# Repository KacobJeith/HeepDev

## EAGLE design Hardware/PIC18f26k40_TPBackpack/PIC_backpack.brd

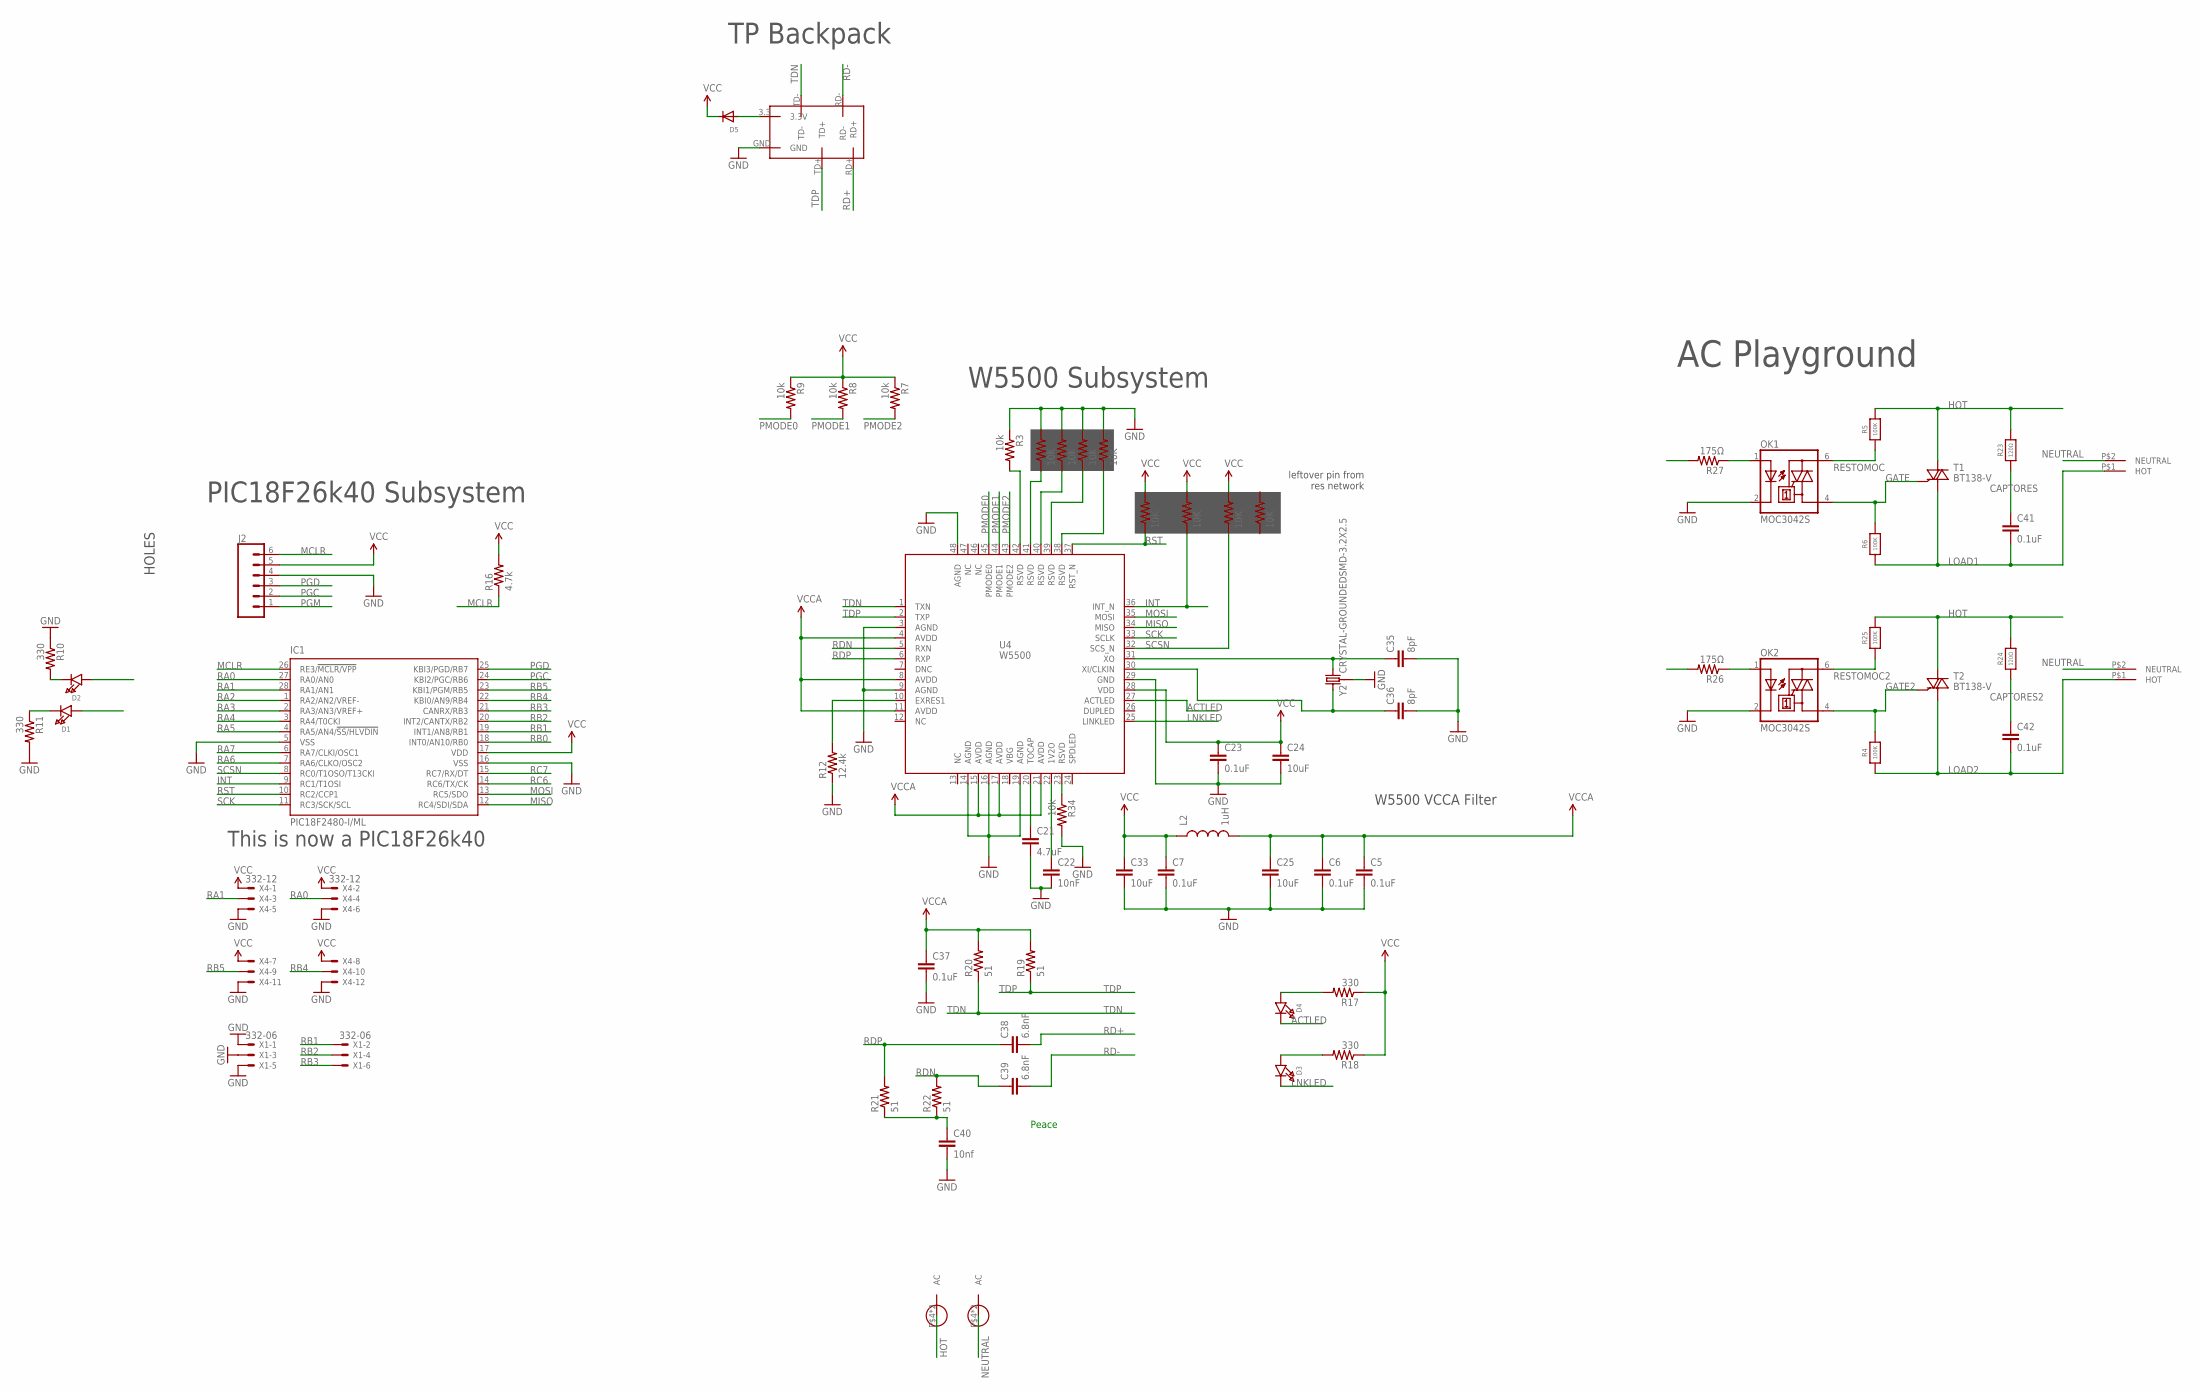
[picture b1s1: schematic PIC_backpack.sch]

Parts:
C5, C6, C7, C23, C37: 0.1uF; 0603-CAP
C21: 4.7uF; 0603-CAP
C22: 10nF; 0603-CAP
C24, C25, C33: 10uF; 0603-CAP
C35, C36: 8pF; 0603-CAP
C38, C39: 6.8nF; 0603-CAP
C40: 10nf; 0603-CAP
C41, C42: 0.1uF; 1210
D1, D2, D3, D4: LED0603_NOOUTLINE; CHIPLED_0603_NOOUTLINE
D5: DIODESOD-123; SOD-123
IC1: PIC18F2480-I/ML; QFN28-ML_6X6MM
J2: CONN_06NO_SILK_FEMALE_PTH; 1X06_NO_SILK
L2: 1uH; 0603
OK1, OK2: MOC3042S; DIL6-SMD
R1, R2: 10K; RESPACK_4X0603
R3, R7, R8, R9, R34: 10k; 0603-RES
R4, R5, R6, R25: 100K; 0805_10MGAP
R10, R11, R17, R18: 330; 0603-RES
R12: 12.4k; 0603-RES
R16: 4.7k; 0603-RES
R19, R20, R21, R22: 51; 0603-RES
R23, R24: 120Ω; 0805_10MGAP
R26, R27: 175Ω; 0603-RES
T1, T2: BT138-V; TO220BV
U4: W5500
U$1: TPLINK_BACKPACK; BACKPACK_WITH_PROTO
U$2, U$3: AC_BLADE
U$4, U$5: AC_TERMINAL
X1: 332-06
X4: 332-12
Y2: CRYSTAL-GROUNDEDSMD-3.2X2.5; CRYSTAL-SMD-3.2X2.5MM

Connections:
ACTLED: D4.C, U4.27 (ACTLED)
CAPTORES: C41.1, R23.1
CAPTORES2: C42.1, R24.1
GATE: OK1.4 (A1), R6.2, T1.G
GATE2: OK2.4 (A1), R4.2, T2.G
GND: C5.2, C6.2, C7.2, C21.2, C22.2, C23.2, C24.2, C25.2, C33.2, C35.2, C36.2, C37.2, C40.2, IC1.5 (VSS), IC1.16 (VSS), J2.4, OK1.2 (C), OK2.2 (C), R1.5 (2), R1.6 (2), R1.7 (2), R1.8 (2), R3.1, R10.1, R11.2, R12.1, R34.2, U4.3 (AGND), U4.9 (AGND), U4.14 (AGND), U4.16 (AGND), U4.19 (AGND), U4.29 (GND), U4.48 (AGND), U$1.GND, X1.1, X1.3, X1.5, X4.5, X4.6, X4.11, X4.12, Y2.2 (3), Y2.4 (3)
HOT: R5.2, R23.2, R24.2, R25.2, T1.T2 (A2), T2.T2 (A2), U$2.P$4, U$2.P$5
INT: IC1.9 (RC1/T1OSI), R2.3 (1), U4.36 (INT_N)
LNKLED: D3.C, U4.25 (LINKLED)
LOAD1: C41.2, R6.1, T1.T1 (A1), U$5.P$1 (HOT)
LOAD2: C42.2, R4.1, T2.T1 (A1), U$4.P$1 (HOT)
MCLR: IC1.26 (RE3/!MCLR/VPP), J2.6, R16.1
MISO: IC1.12 (RC4/SDI/SDA), U4.34 (MISO)
MOSI: IC1.13 (RC5/SDO), U4.35 (MOSI)
unnamed: R3.2, U4.42 (RSVD)
unnamed: D2.C, R10.2
unnamed: C21.1, U4.20 (TOCAP)
unnamed: D1.C, R11.1
unnamed: C22.1, U4.22 (1V2O)
unnamed: R12.2, U4.10 (EXRES1)
unnamed: D4.A, R17.2
unnamed: D3.A, R18.2
unnamed: D5.A, U$1.3.3 (3.3V)
unnamed: C40.1, R21.1, R22.1
unnamed: R1.1, U4.41 (RSVD)
unnamed: R1.3 (1), U4.39 (RSVD)
unnamed: R1.2 (1), U4.40 (RSVD)
unnamed: R1.4 (1), U4.38 (RSVD)
unnamed: R34.1, U4.23 (RSVD)
unnamed: C35.1, U4.31 (XO), Y2.3 (2)
unnamed: C36.1, U4.30 (XI/CLKIN), Y2.1
unnamed: OK1.1 (A), R27.1
unnamed: OK2.1 (A), R26.1
NEUTRAL: U$3.P$4, U$3.P$5, U$4.P$2 (NEUTRAL), U$5.P$2 (NEUTRAL)
PGC: IC1.24 (KBI2/PGC/RB6), J2.2
PGD: IC1.25 (KBI3/PGD/RB7), J2.3
PGM: J2.1
PMODE0: R9.2, U4.45 (PMODE0)
PMODE1: R8.2, U4.44 (PMODE1)
PMODE2: R7.2, U4.43 (PMODE2)
RA0: IC1.27 (RA0/AN0), X4.4
RA1: IC1.28 (RA1/AN1), X4.3
RA2: IC1.1 (RA2/AN2/VREF-)
RA3: IC1.2 (RA3/AN3/VREF+)
RA4: IC1.3 (RA4/T0CKI), R26.2
RA5: IC1.4 (RA5/AN4/!SS/HLVDIN), R27.2
RA6: IC1.7 (RA6/CLKO/OSC2)
RA7: IC1.6 (RA7/CLKI/OSC1)
RB0: IC1.18 (INT0/AN10/RB0)
RB1: IC1.19 (INT1/AN8/RB1), X1.2
RB2: IC1.20 (INT2/CANTX/RB2), X1.4
RB3: IC1.21 (CANRX/RB3), X1.6
RB4: IC1.22 (KBI0/AN9/RB4), X4.10
RB5: IC1.23 (KBI1/PGM/RB5), X4.9
RC6: D2.A, IC1.14 (RC6/TX/CK)
RC7: D1.A, IC1.15 (RC7/RX/DT)
RD+: C38.2, U$1.RD+
RD-: C39.2, U$1.RD-
RDN: C39.1, R22.2, U4.5 (RXN)
RDP: C38.1, R21.2, U4.6 (RXP)
RESTOMOC: OK1.6 (A2), R5.1
RESTOMOC2: OK2.6 (A2), R25.1
RST: IC1.10 (RC2/CCP1), R2.2 (1), U4.37 (RST_N)
SCK: IC1.11 (RC3/SCK/SCL), U4.33 (SCLK)
SCSN: IC1.8 (RC0/T1OSO/T13CKI), R2.4 (1), U4.32 (SCS_N)
TDN: R20.1, U4.1 (TXN), U$1.TD-
TDP: R19.1, U4.2 (TXP), U$1.TD+
VCC: C7.1, C23.1, C24.1, C33.1, D5.C, IC1.17 (VDD), J2.5, L2.1, R2.5 (2), R2.6 (2), R2.7 (2), R7.1, R8.1, R9.1, R16.2, R17.1, R18.1, U4.28 (VDD), X4.1, X4.2, X4.7, X4.8
VCCA: C5.1, C6.1, C25.1, C37.1, L2.2, R19.2, R20.2, U4.4 (AVDD), U4.8 (AVDD), U4.11 (AVDD), U4.15 (AVDD), U4.17 (AVDD), U4.21 (AVDD)

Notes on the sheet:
This is now a PIC18F26k40
PIC18F26k40 Subsystem
W5500 Subsystem
W5500 VCCA Filter
AC Playground
TP Backpack
leftover pin from res network
Peace
HOLES

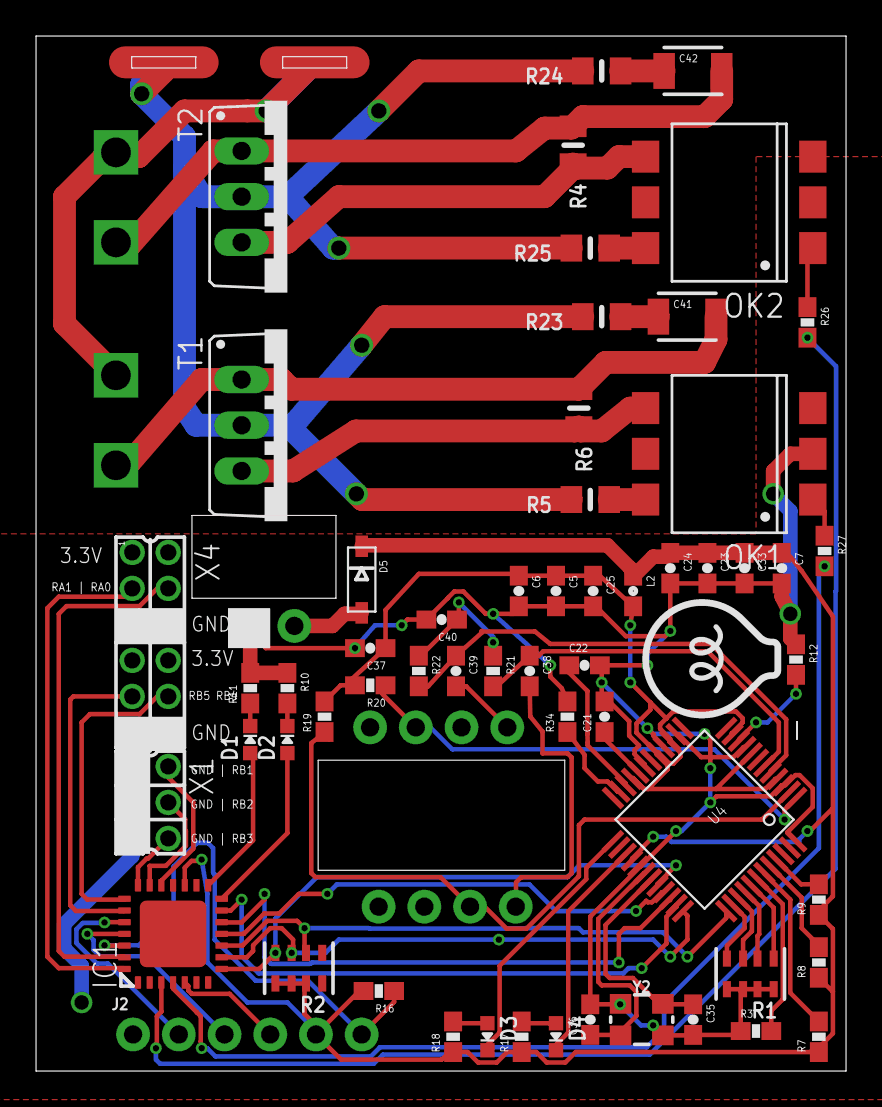
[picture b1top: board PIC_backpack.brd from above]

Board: 2 copper layers, 45.0 x 57.5 mm, 64 parts (0 on the bottom side), 63 nets.

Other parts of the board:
U$10: HEEPLOGOSMALL

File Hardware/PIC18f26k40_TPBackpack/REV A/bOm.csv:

Part,     Value ,                      Package    ,            Library             

C5  ,   0.1uF                      , 0603-CAP               , SparkFun-Passives   
C6  ,   0.1uF                      , 0603-CAP               , SparkFun-Passives   
C7  ,   0.1uF                      , 0603-CAP               , SparkFun-Passives   
C21 ,   4.7uF                      , 0603-CAP               , SparkFun-Passives   
C22 ,   10nF                       , 0603-CAP               , SparkFun-Passives   
C23 ,   0.1uF                      , 0603-CAP               , SparkFun-Passives   
C24 ,   10uF                       , 0603-CAP               , SparkFun-Passives   
C25 ,   10uF                       , 0603-CAP               , SparkFun-Passives   
C33 ,   10uF                       , 0603-CAP               , SparkFun-Passives   
C35 ,   8pF                        , 0603-CAP               , SparkFun-Passives   
C36 ,   8pF                        , 0603-CAP               , SparkFun-Passives   
C37 ,   0.1uF                      , 0603-CAP               , SparkFun-Passives   
C38 ,   6.8nF                      , 0603-CAP               , SparkFun-Passives   
C39 ,   6.8nF                      , 0603-CAP               , SparkFun-Passives   
C40 ,   10nf                       , 0603-CAP               , SparkFun-Passives   
C41 ,   0.1uF                      , 1210                   , SparkFun-Capacitors 
C42 ,   0.1uF                      , 1210                   , SparkFun-Capacitors 
D1  ,                              , CHIPLED_0603_NOOUTLINE , microbuilder        
D2  ,                              , CHIPLED_0603_NOOUTLINE , microbuilder        
D3  ,                              , CHIPLED_0603_NOOUTLINE , microbuilder        
D4  ,                              , CHIPLED_0603_NOOUTLINE , microbuilder        
D5  ,                              , SOD-123                , adafruit            
IC1 ,   PIC18F2480-I/ML            , QFN28-ML_6X6MM         , microchip           
J2  ,                              , 1X06_NO_SILK           , SparkFun-Connectors 
L2  ,   1uH                        , 0603                   , SparkFun-Passives   
OK1 ,   MOC3042S                   , DIL6-SMD               , optocoupler         
OK2 ,   MOC3042S                   , DIL6-SMD               , optocoupler         
R1  ,   10K                        , RESPACK_4X0603         , microbuilder        
R2  ,   10K                        , RESPACK_4X0603         , microbuilder        
R3  ,   10k                        , 0603-RES               , SparkFun-Passives   
R4  ,   100K                       , 0805_10MGAP            , microbuilder        
R5  ,   100K                       , 0805_10MGAP            , microbuilder        
R6  ,   100K                       , 0805_10MGAP            , microbuilder        
R7  ,   10k                        , 0603-RES               , SparkFun-Passives   
R8  ,   10k                        , 0603-RES               , SparkFun-Passives   
R9  ,   10k                        , 0603-RES               , SparkFun-Passives   
R10 ,   330                        , 0603-RES               , SparkFun-Passives   
R11 ,   330                        , 0603-RES               , SparkFun-Passives   
R12 ,   12.4k                      , 0603-RES               , SparkFun-Passives   
R16 ,   4.7k                       , 0603-RES               , SparkFun-Passives   
R17 ,   330                        , 0603-RES               , SparkFun-Passives   
R18 ,   330                        , 0603-RES               , SparkFun-Passives   
R19 ,   51                         , 0603-RES               , SparkFun-Passives   
R20 ,   51                         , 0603-RES               , SparkFun-Passives   
R21 ,   51                         , 0603-RES               , SparkFun-Passives   
R22 ,   51                         , 0603-RES               , SparkFun-Passives   
R23 ,   120?                       , 0805_10MGAP            , microbuilder        
R24 ,   120?                       , 0805_10MGAP            , microbuilder        
R25 ,   100K                       , 0805_10MGAP            , microbuilder        
R26 ,   175?                       , 0603-RES               , SparkFun-Passives   
R27 ,   175?                       , 0603-RES               , SparkFun-Passives   
R34 ,   10k                        , 0603-RES               , SparkFun-Passives   
T1  ,   BT138-V                    , TO220BV                , triac               
T2  ,   BT138-V                    , TO220BV                , triac               
U$1 ,   TPLINK_BACKPACK            , BACKPACK_WITH_PROTO    , Heep                
U$2 ,   AC_BLADE                   , AC_BLADE               , Heep                
U$3 ,   AC_BLADE                   , AC_BLADE               , Heep                
U$4 ,   AC_TERMINAL                , AC_TERMINAL            , Heep                
U$5 ,   AC_TERMINAL                , AC_TERMINAL            , Heep                
U4  ,   W5500                      , W5500                  , W5500               
X1  ,   332-06                     , 332-06                 , con-garry           
X4  ,   332-12                     , 332-12                 , con-garry           
Y2  ,   CRYSTAL-GROUNDEDSMD-3.2X2.5, CRYSTAL-SMD-3.2X2.5MM  , SparkFun-Clocks     
,

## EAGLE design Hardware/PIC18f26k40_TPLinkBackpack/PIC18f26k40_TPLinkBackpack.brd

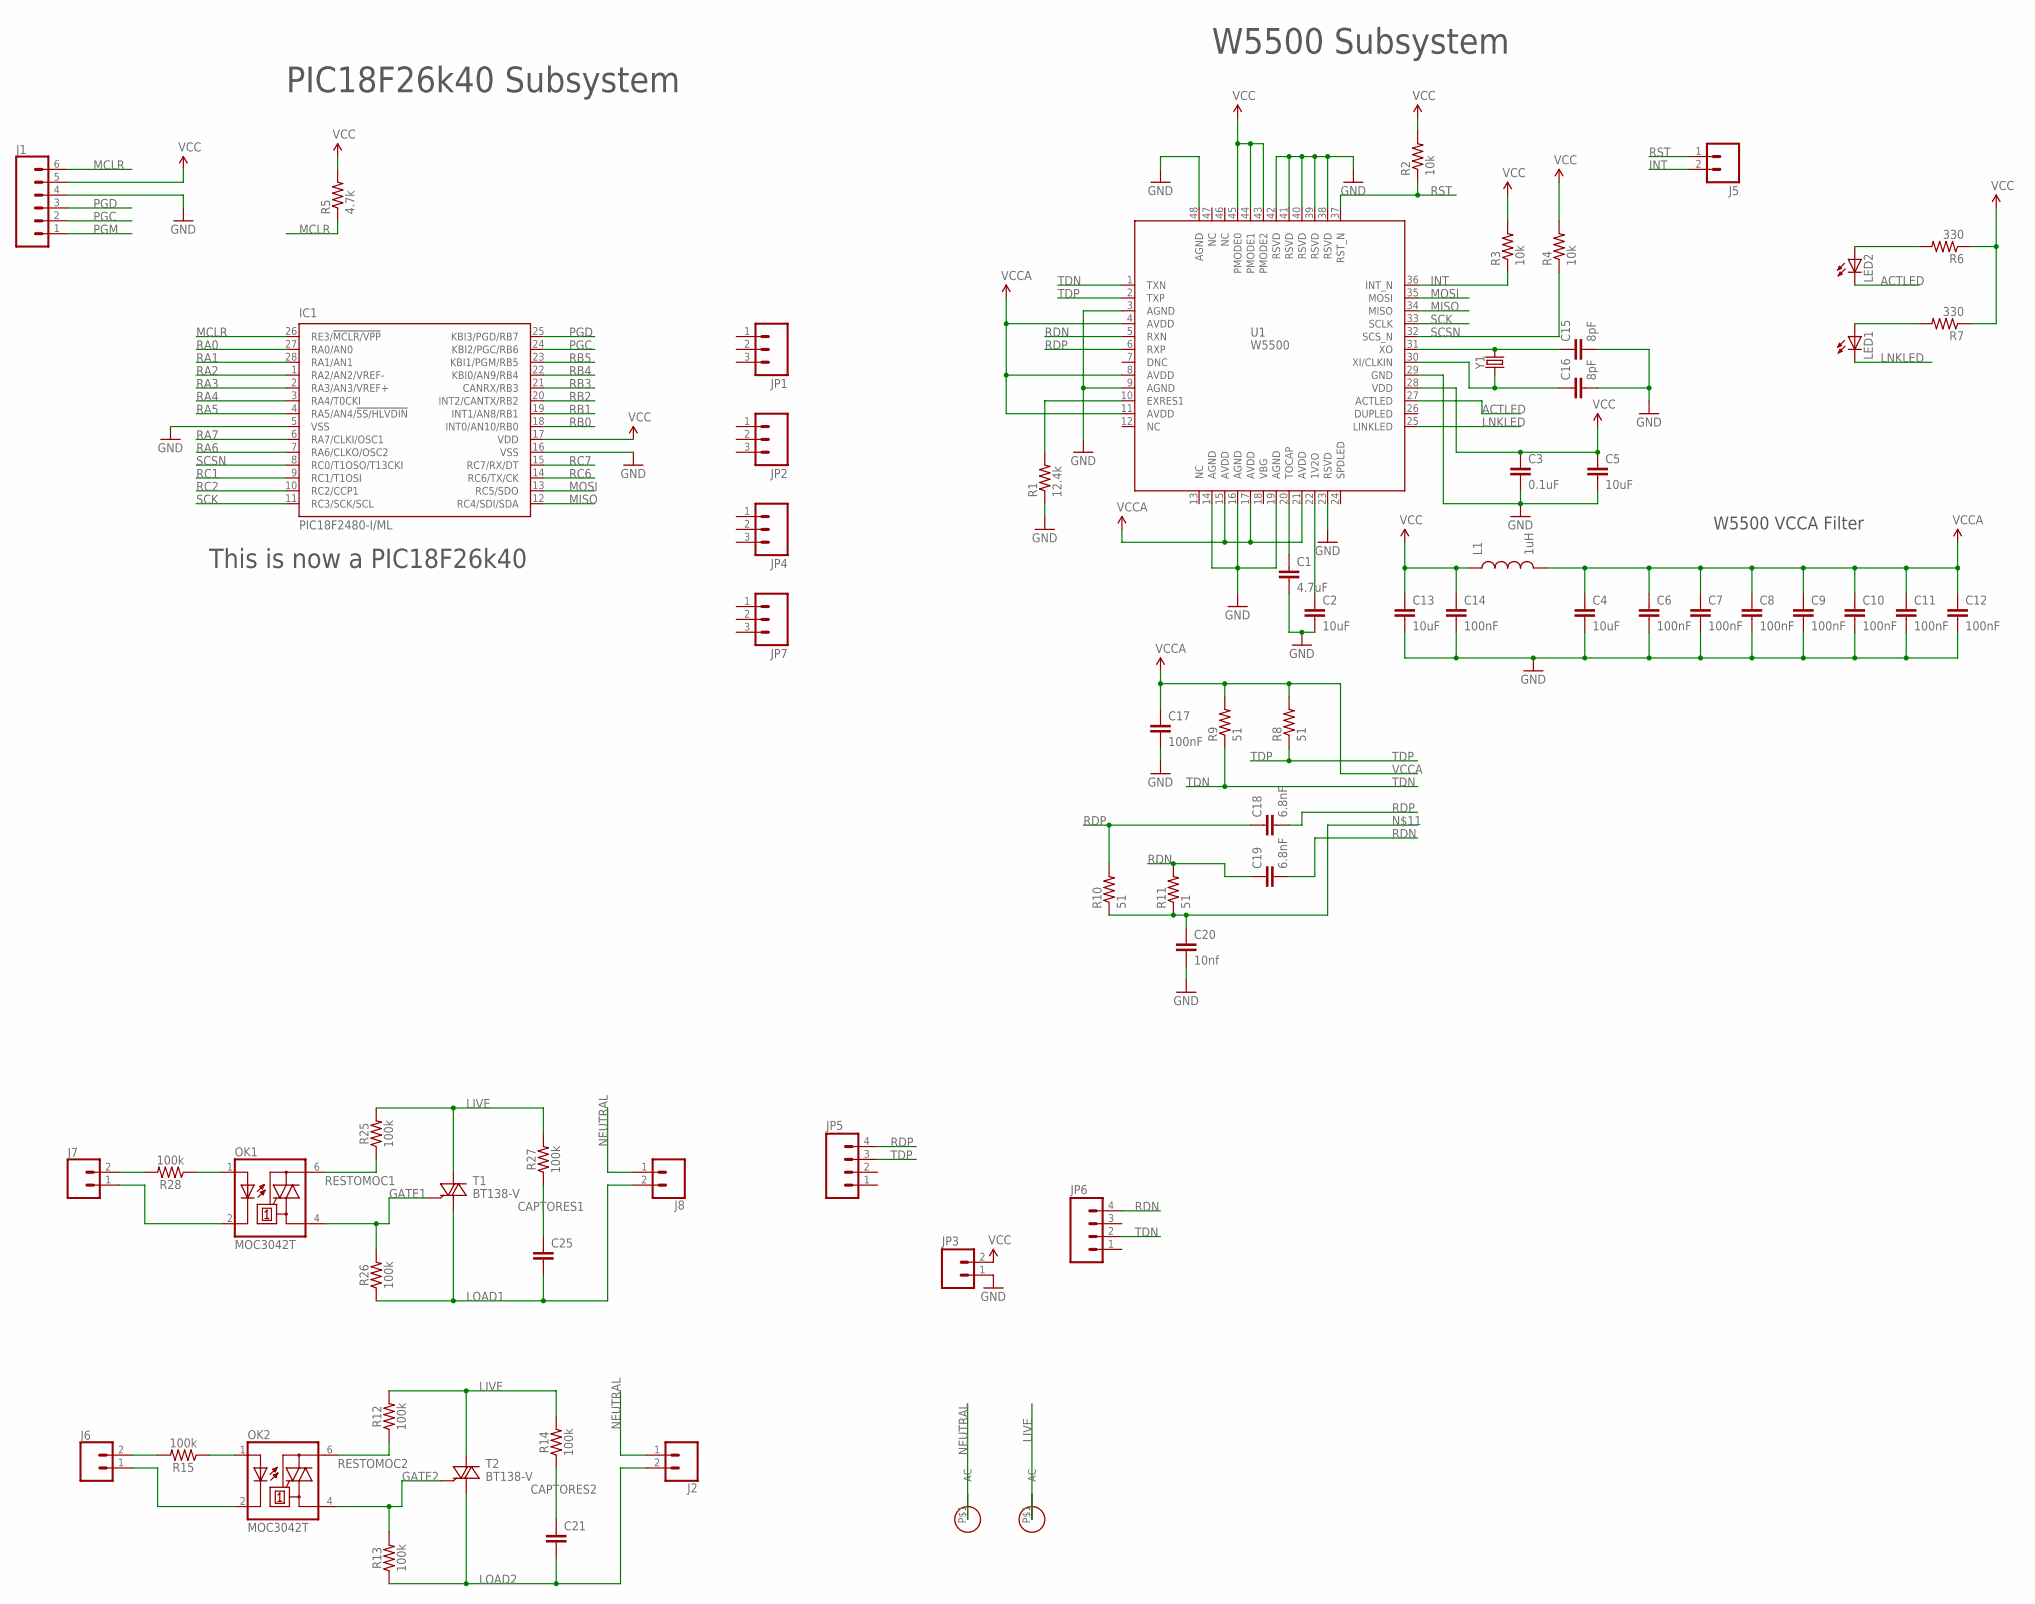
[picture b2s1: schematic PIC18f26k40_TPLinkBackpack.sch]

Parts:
AC_L: AC_BLADE
AC_N: AC_BLADE
C1: 4.7uF; 0603-CAP
C2, C4, C5, C13: 10uF; 0603-CAP
C3: 0.1uF; 0603-CAP
C6, C7, C8, C9, C10, C11, C12, C14, C17: 100nF; 0603-CAP
C15, C16: 8pF; 0603-CAP
C18, C19: 6.8nF; 0603-CAP
C20: 10nf; 0603-CAP
C21, C25: CAP0603-CAP; 0603-CAP
IC1: PIC18F2480-I/ML; QFN28-ML_6X6MM
J1: CONN_06NO_SILK_FEMALE_PTH; 1X06_NO_SILK
J2, J8: CONN_025MM; SCREWTERMINAL-5MM-2
J5: M02PTH; 1X02@1
J6, J7: CONN_02; 1X02
JP1, JP2, JP4, JP7: M03LONGPADS; 1X03_LONGPADS
JP3: M021X02_NO_SILK; 1X02_NO_SILK@1
JP5, JP6: M04NO_SILK_ALL_ROUND; 1X04_NO_SILK_ALL_ROUND
L1: 1uH; 0603
LED1, LED2: LEDCHIP-LED0805; CHIP-LED0805
OK1, OK2: MOC3042T; DIL06B
R1: 12.4k; 0603-RES
R2, R3, R4: 10k; 0603-RES
R5: 4.7k; 0603-RES
R6, R7: 330; 0603-RES
R8, R9, R10, R11: 51; 0603-RES
R12, R13, R14, R15, R25, R26, R27, R28: 100k; 0603
T1, T2: BT138-V; TO220BV
U1: W5500
Y1: CRYSTALSMD-3.2X2.5; CRYSTAL-SMD-3.2X2.5MM

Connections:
ACTLED: LED2.C, U1.27 (ACTLED)
CAPTORES1: C25.1, R27.1
CAPTORES2: C21.1, R14.1
GATE1: OK1.4 (A1), R26.2, T1.G
GATE2: OK2.4 (A1), R13.2, T2.G
GND: C1.2, C2.2, C3.2, C4.2, C5.2, C6.2, C7.2, C8.2, C9.2, C10.2, C11.2, C12.2, C13.2, C14.2, C15.2, C16.2, C17.2, C20.2, IC1.5 (VSS), IC1.16 (VSS), J1.4, JP3.1, R1.1, U1.3 (AGND), U1.9 (AGND), U1.14 (AGND), U1.16 (AGND), U1.19 (AGND), U1.23 (RSVD), U1.29 (GND), U1.38 (RSVD), U1.39 (RSVD), U1.40 (RSVD), U1.41 (RSVD), U1.42 (RSVD), U1.48 (AGND)
INT: J5.2, R3.1, U1.36 (INT_N)
LIVE: AC_L.P$1, R12.2, R14.2, R25.2, R27.2, T1.T2 (A2), T2.T2 (A2)
LNKLED: LED1.C, U1.25 (LINKLED)
LOAD1: C25.2, J8.2, R26.1, T1.T1 (A1)
LOAD2: C21.2, J2.2, R13.1, T2.T1 (A1)
MCLR: IC1.26 (RE3/!MCLR/VPP), J1.6, R5.1
MISO: IC1.12 (RC4/SDI/SDA), U1.34 (MISO)
MOSI: IC1.13 (RC5/SDO), U1.35 (MOSI)
unnamed: C1.1, U1.20 (TOCAP)
unnamed: C2.1, U1.22 (1V2O)
unnamed: J7.2, R28.2
unnamed: R1.2, U1.10 (EXRES1)
unnamed: C15.1, U1.31 (XO), Y1.3 (2)
unnamed: C16.1, U1.30 (XI/CLKIN), Y1.1
unnamed: LED2.A, R6.2
unnamed: J6.2, R15.2
unnamed: LED1.A, R7.2
unnamed: OK2.1 (A), R15.1
unnamed: C20.1, R10.1, R11.1
unnamed: J6.1, OK2.2 (C)
unnamed: OK1.1 (A), R28.1
unnamed: J7.1, OK1.2 (C)
NEUTRAL: AC_N.P$1, J2.1, J8.1
PGC: IC1.24 (KBI2/PGC/RB6), J1.2
PGD: IC1.25 (KBI3/PGD/RB7), J1.3
PGM: J1.1
RA0: IC1.27 (RA0/AN0)
RA1: IC1.28 (RA1/AN1)
RA2: IC1.1 (RA2/AN2/VREF-)
RA3: IC1.2 (RA3/AN3/VREF+)
RA4: IC1.3 (RA4/T0CKI)
RA5: IC1.4 (RA5/AN4/!SS/HLVDIN)
RA6: IC1.7 (RA6/CLKO/OSC2)
RA7: IC1.6 (RA7/CLKI/OSC1)
RB0: IC1.18 (INT0/AN10/RB0)
RB1: IC1.19 (INT1/AN8/RB1)
RB2: IC1.20 (INT2/CANTX/RB2)
RB3: IC1.21 (CANRX/RB3)
RB4: IC1.22 (KBI0/AN9/RB4)
RB5: IC1.23 (KBI1/PGM/RB5)
RC1: IC1.9 (RC1/T1OSI)
RC2: IC1.10 (RC2/CCP1)
RC6: IC1.14 (RC6/TX/CK)
RC7: IC1.15 (RC7/RX/DT)
RDN: C19.1, C19.2, JP6.4, R11.2, U1.5 (RXN)
RDP: C18.1, C18.2, JP5.4, R10.2, U1.6 (RXP)
RESTOMOC1: OK1.6 (A2), R25.1
RESTOMOC2: OK2.6 (A2), R12.1
RST: J5.1, R2.1, U1.37 (RST_N)
SCK: IC1.11 (RC3/SCK/SCL), U1.33 (SCLK)
SCSN: IC1.8 (RC0/T1OSO/T13CKI), R4.1, U1.32 (SCS_N)
TDN: JP6.2, R9.1, U1.1 (TXN)
TDP: JP5.3, R8.1, U1.2 (TXP)
VCC: C3.1, C5.1, C13.1, C14.1, IC1.17 (VDD), J1.5, JP3.2, L1.1, R2.2, R3.2, R4.2, R5.2, R6.1, R7.1, U1.28 (VDD), U1.43 (PMODE2), U1.44 (PMODE1), U1.45 (PMODE0)
VCCA: C4.1, C6.1, C7.1, C8.1, C9.1, C10.1, C11.1, C12.1, C17.1, L1.2, R8.2, R9.2, U1.4 (AVDD), U1.8 (AVDD), U1.11 (AVDD), U1.15 (AVDD), U1.17 (AVDD), U1.21 (AVDD)

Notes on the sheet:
This is now a PIC18F26k40
PIC18F26k40 Subsystem
W5500 Subsystem
W5500 VCCA Filter

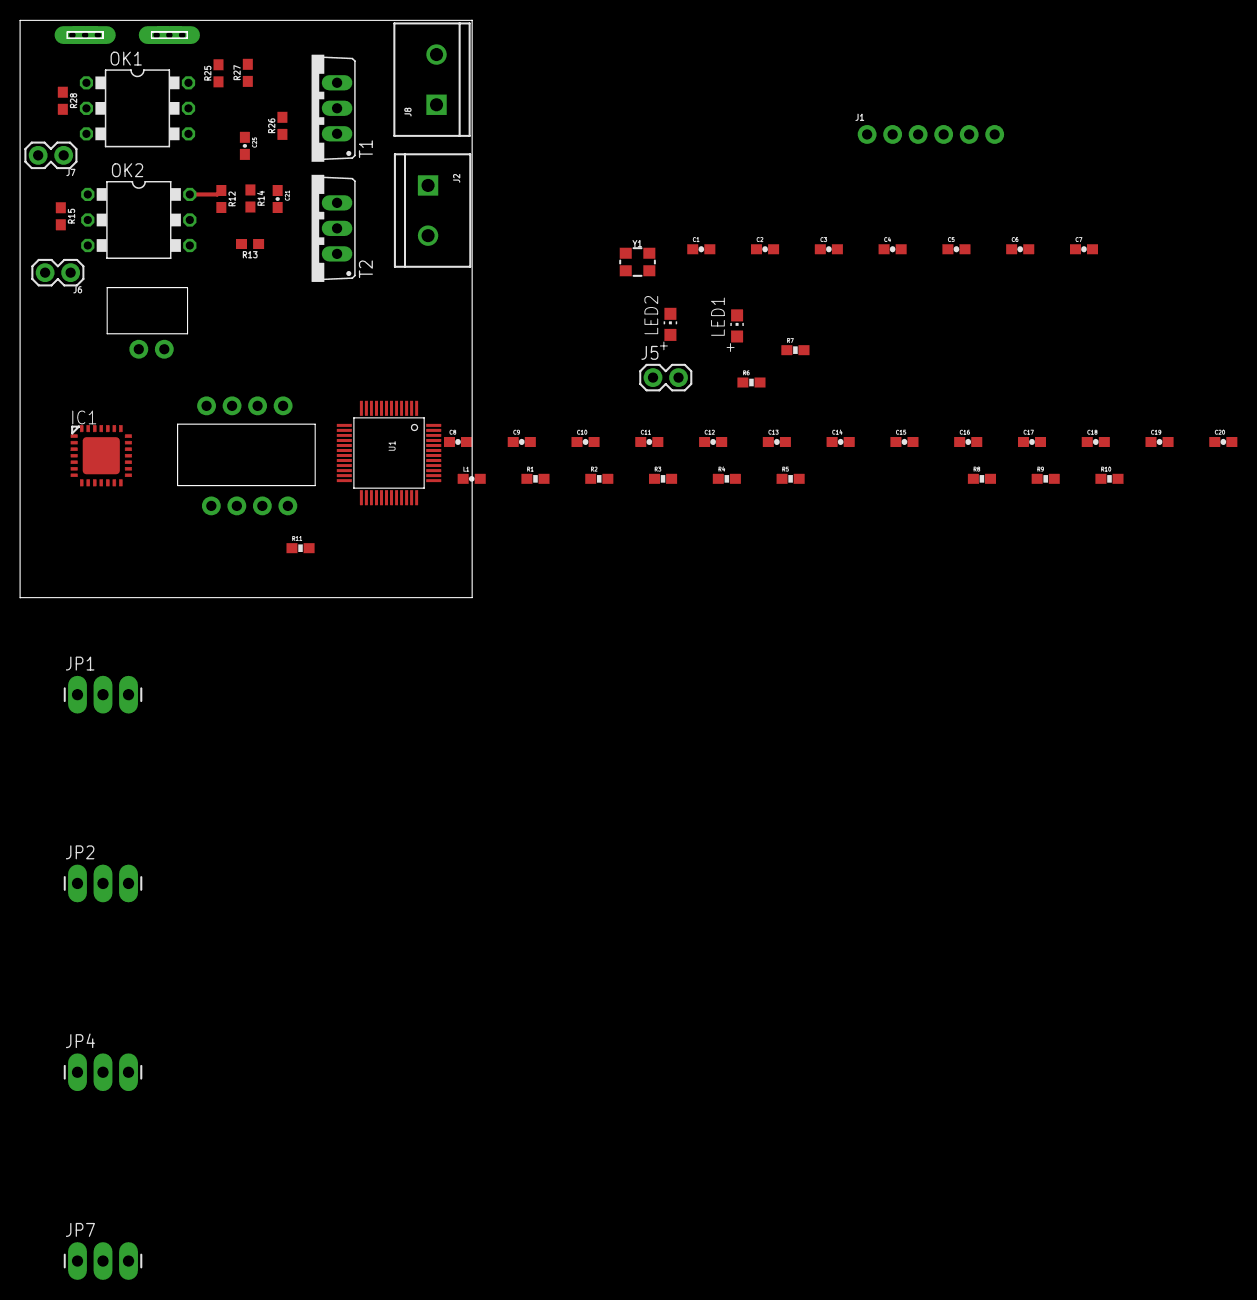
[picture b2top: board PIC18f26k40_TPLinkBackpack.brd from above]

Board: 2 copper layers, 45.0 x 57.5 mm, 66 parts (0 on the bottom side), 42 nets.

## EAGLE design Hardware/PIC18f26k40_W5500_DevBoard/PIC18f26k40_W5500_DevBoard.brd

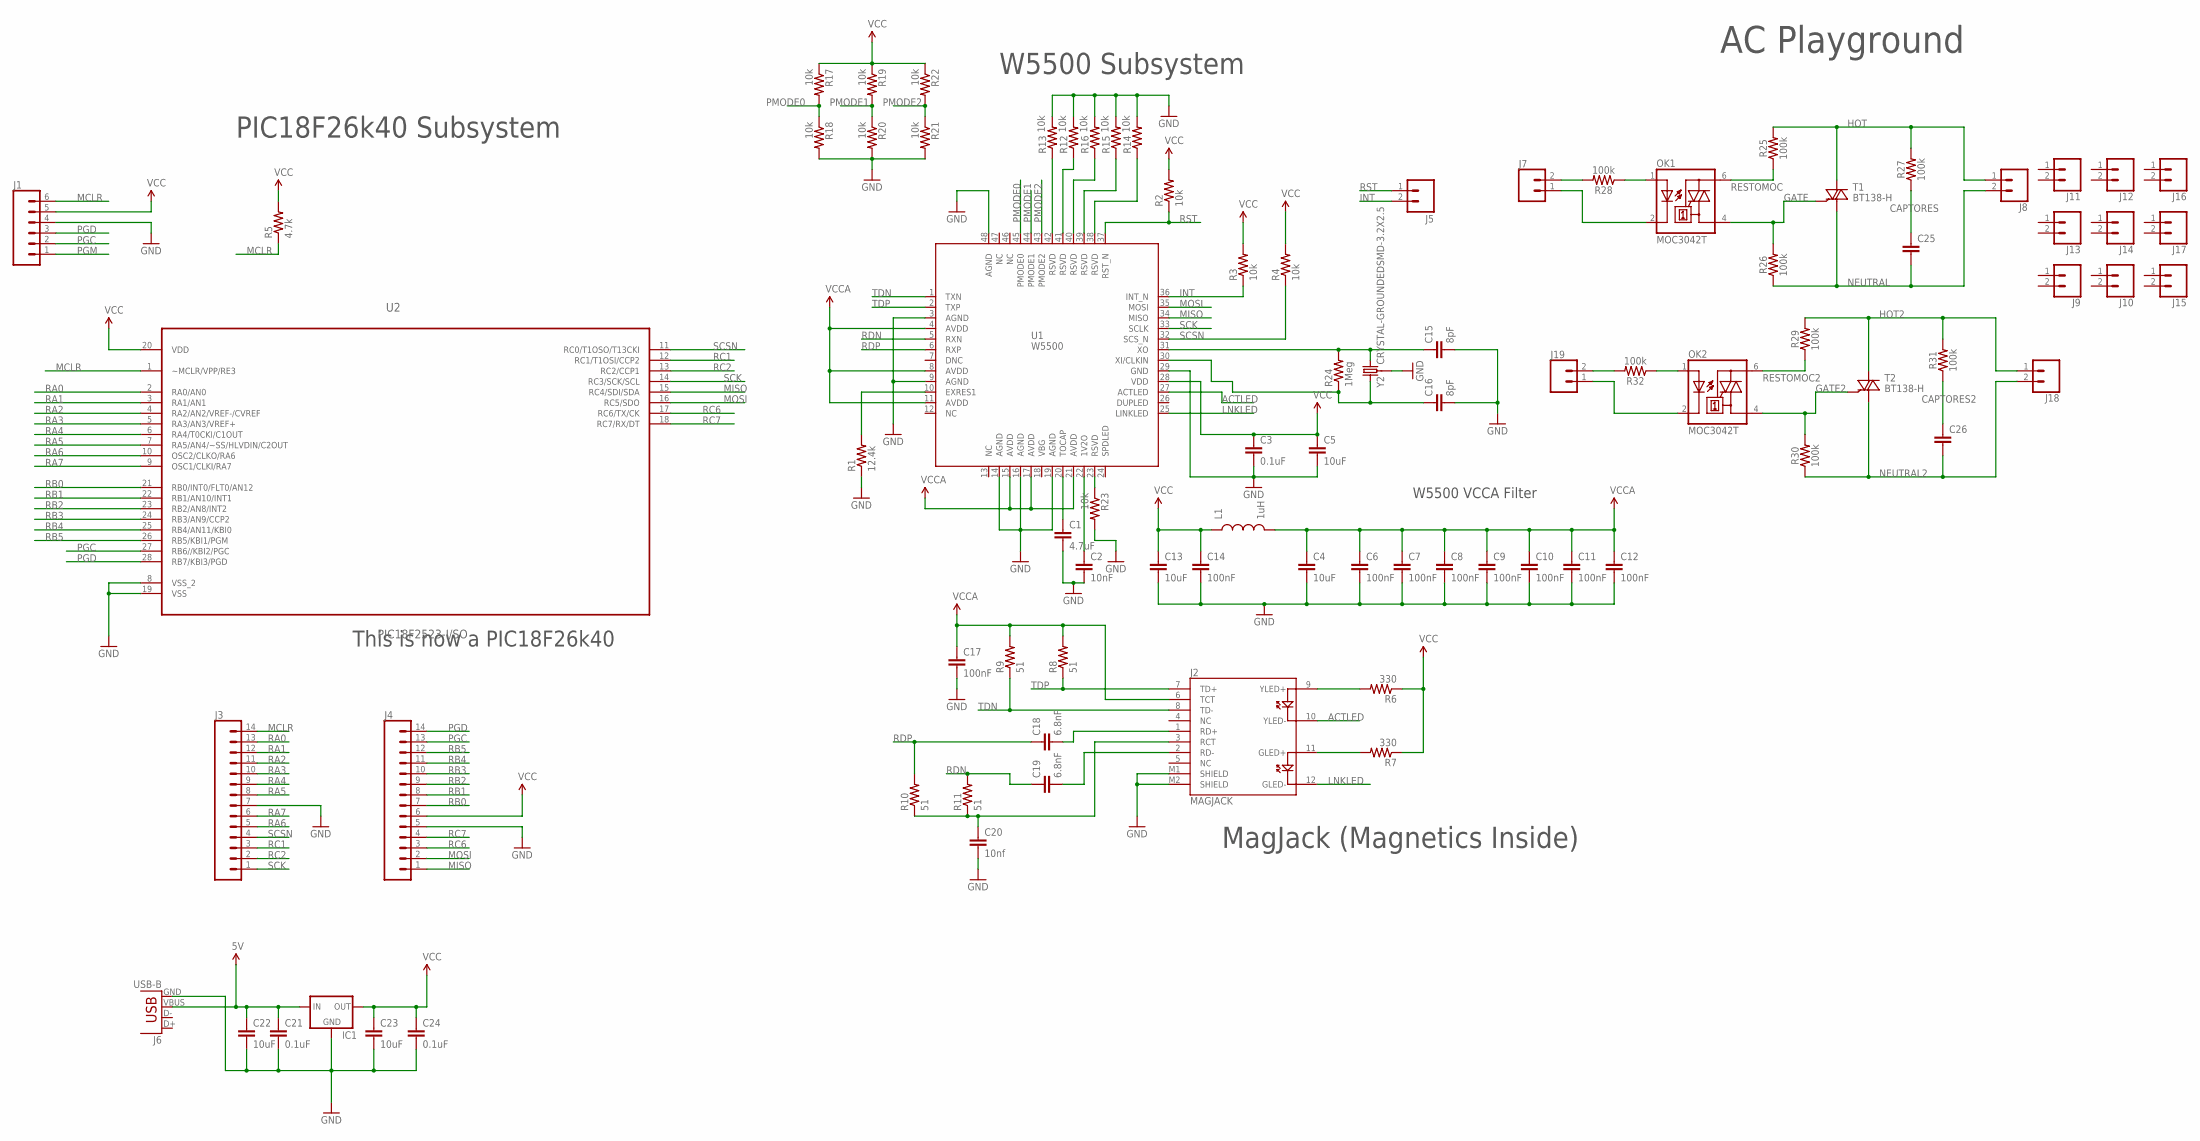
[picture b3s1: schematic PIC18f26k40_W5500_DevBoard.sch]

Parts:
C1: 4.7uF; 0603-CAP
C2: 10nF; 0603-CAP
C3, C21, C24: 0.1uF; 0603-CAP
C4, C5, C13, C22, C23: 10uF; 0603-CAP
C6, C7, C8, C9, C10, C11, C12, C14, C17: 100nF; 0603-CAP
C15, C16: 8pF; 0603-CAP
C18, C19: 6.8nF; 0603-CAP
C20: 10nf; 0603-CAP
C25, C26: CAPPTH3; CAP-PTH-LARGE
IC1: 78XXL
J1: CONN_06NO_SILK_FEMALE_PTH; 1X06_NO_SILK
J2: MAGJACK
J3, J4: CONN_14; 1X14
J5: M02PTH; 1X02@1
J6: USB-B; USB-B-PTH
J7, J19: CONN_02; 1X02
J8, J9, J10, J11, J12, J13, J14, J15, J16, J17, J18: CONN_025MM; SCREWTERMINAL-5MM-2
L1: 1uH; 0603
OK1, OK2: MOC3042T; DIL06B
R1: 12.4k; 0603-RES
R2, R3, R4, R12, R13, R14, R15, R16, R17, R18, R19, R20, R21, R22, R23: 10k; 0603-RES
R5: 4.7k; 0603-RES
R6, R7: 330; 0603-RES
R8, R9, R10, R11: 51; 0603-RES
R24: 1Meg; 0603-RES
R25, R26, R27, R28, R29, R30, R31, R32: 100k; AXIAL-0.3
T1, T2: BT138-H; TO220BH
U1: W5500
U2: PIC18F2523-I/SO; SOIC127P1030X265-28N
Y2: CRYSTAL-GROUNDEDSMD-3.2X2.5; CRYSTAL-SMD-3.2X2.5MM

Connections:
5V: C21.1, C22.1, IC1.IN, J6.VBUS
ACTLED: J2.10 (YLED-), U1.27 (ACTLED)
CAPTORES: C25.1, R27.P$1 (1)
CAPTORES2: C26.1, R31.P$1 (1)
GATE: OK1.4 (A1), R26.P$2 (2), T1.G
GATE2: OK2.4 (A1), R30.P$2 (2), T2.G
GND: C1.2, C2.2, C3.2, C4.2, C5.2, C6.2, C7.2, C8.2, C9.2, C10.2, C11.2, C12.2, C13.2, C14.2, C15.2, C16.2, C17.2, C20.2, C21.2, C22.2, C23.2, C24.2, IC1.GND, J1.4, J2.M1 (SHIELD), J2.M2 (SHIELD), J3.7, J4.5, J6.GND, R1.1, R12.2, R13.2, R14.2, R15.2, R16.2, R18.2, R20.2, R21.2, R23.2, U1.3 (AGND), U1.9 (AGND), U1.14 (AGND), U1.16 (AGND), U1.19 (AGND), U1.29 (GND), U1.48 (AGND), U2.8 (VSS_2), U2.19 (VSS), Y2.2 (3), Y2.4 (3)
HOT: J8.1, R25.P$2 (2), R27.P$2 (2), T1.T2 (A2)
HOT2: J18.1, R29.P$2 (2), R31.P$2 (2), T2.T2 (A2)
INT: J5.2, R3.1, U1.36 (INT_N)
LNKLED: J2.12 (GLED-), U1.25 (LINKLED)
MCLR: J1.6, J3.14, R5.1, U2.1 (~MCLR/VPP/RE3)
MISO: J4.1, U1.34 (MISO), U2.15 (RC4/SDI/SDA)
MOSI: J4.2, U1.35 (MOSI), U2.16 (RC5/SDO)
unnamed: C1.1, U1.20 (TOCAP)
unnamed: C2.1, U1.22 (1V2O)
unnamed: R12.1, U1.41 (RSVD)
unnamed: R1.2, U1.10 (EXRES1)
unnamed: J7.2, R28.P$2 (2)
unnamed: C15.1, R24.2, U1.31 (XO), Y2.3 (2)
unnamed: J2.9 (YLED+), R6.2
unnamed: C18.2, J2.1 (RD+)
unnamed: J2.11 (GLED+), R7.2
unnamed: C19.2, J2.2 (RD-)
unnamed: C20.1, J2.3 (RCT), R10.1, R11.1
unnamed: R14.1, U1.38 (RSVD)
unnamed: R15.1, U1.39 (RSVD)
unnamed: R16.1, U1.40 (RSVD)
unnamed: R13.1, U1.42 (RSVD)
unnamed: R23.1, U1.23 (RSVD)
unnamed: C16.1, R24.1, U1.30 (XI/CLKIN), Y2.1
unnamed: OK1.1 (A), R28.P$1 (1)
unnamed: J7.1, OK1.2 (C)
unnamed: J19.2, R32.P$2 (2)
unnamed: OK2.1 (A), R32.P$1 (1)
unnamed: J19.1, OK2.2 (C)
NEUTRAL: C25.2, J8.2, R26.P$1 (1), T1.T1 (A1)
NEUTRAL2: C26.2, J18.2, R30.P$1 (1), T2.T1 (A1)
PGC: J1.2, J4.13, U2.27 (RB6//KBI2/PGC)
PGD: J1.3, J4.14, U2.28 (RB7/KBI3/PGD)
PGM: J1.1
PMODE0: R17.2, R18.1, U1.45 (PMODE0)
PMODE1: R19.2, R20.1, U1.44 (PMODE1)
PMODE2: R21.1, R22.2, U1.43 (PMODE2)
RA0: J3.13, U2.2 (RA0/AN0)
RA1: J3.12, U2.3 (RA1/AN1)
RA2: J3.11, U2.4 (RA2/AN2/VREF-/CVREF)
RA3: J3.10, U2.5 (RA3/AN3/VREF+)
RA4: J3.9, U2.6 (RA4/T0CKI/C1OUT)
RA5: J3.8, U2.7 (RA5/AN4/~SS/HLVDIN/C2OUT)
RA6: J3.5, U2.10 (OSC2/CLKO/RA6)
RA7: J3.6, U2.9 (OSC1/CLKI/RA7)
RB0: J4.7, U2.21 (RB0/INT0/FLT0/AN12)
RB1: J4.8, U2.22 (RB1/AN10/INT1)
RB2: J4.9, U2.23 (RB2/AN8/INT2)
RB3: J4.10, U2.24 (RB3/AN9/CCP2)
RB4: J4.11, U2.25 (RB4/AN11/KBI0)
RB5: J4.12, U2.26 (RB5/KBI1/PGM)
RC1: J3.3, U2.12 (RC1/T1OSI/CCP2)
RC2: J3.2, U2.13 (RC2/CCP1)
RC6: J4.3, U2.17 (RC6/TX/CK)
RC7: J4.4, U2.18 (RC7/RX/DT)
RDN: C19.1, R11.2, U1.5 (RXN)
RDP: C18.1, R10.2, U1.6 (RXP)
RESTOMOC: OK1.6 (A2), R25.P$1 (1)
RESTOMOC2: OK2.6 (A2), R29.P$1 (1)
RST: J5.1, R2.1, U1.37 (RST_N)
SCK: J3.1, U1.33 (SCLK), U2.14 (RC3/SCK/SCL)
SCSN: J3.4, R4.1, U1.32 (SCS_N), U2.11 (RC0/T1OSO/T13CKI)
TDN: J2.8 (TD-), R9.1, U1.1 (TXN)
TDP: J2.7 (TD+), R8.1, U1.2 (TXP)
VCC: C3.1, C5.1, C13.1, C14.1, C23.1, C24.1, IC1.OUT, J1.5, J4.6, L1.1, R2.2, R3.2, R4.2, R5.2, R6.1, R7.1, R17.1, R19.1, R22.1, U1.28 (VDD), U2.20 (VDD)
VCCA: C4.1, C6.1, C7.1, C8.1, C9.1, C10.1, C11.1, C12.1, C17.1, J2.6 (TCT), L1.2, R8.2, R9.2, U1.4 (AVDD), U1.8 (AVDD), U1.11 (AVDD), U1.15 (AVDD), U1.17 (AVDD), U1.21 (AVDD)

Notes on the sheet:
This is now a PIC18F26k40
PIC18F26k40 Subsystem
W5500 Subsystem
W5500 VCCA Filter
MagJack (Magnetics Inside)
AC Playground

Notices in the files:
parts and their libraries:
SparkFun-Connectors: Licensing: Creative Commons ShareAlike 4.0 International - https://creativecommons.org/licenses/by-sa/4.0
microbuilder: This work is placed in the public domain, and may be freely used for commercial and non-commercial work with the following conditions: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
